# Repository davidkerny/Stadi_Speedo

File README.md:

Varianty pro Stadi_Speedo HW board:
__________________________________

MultiGauge od V1.8:

1. SPÍDO režim: (rychloměr) se ukazuje:
   pokud budík zaznamená jízdu.
   Pokud nějaké zaznamenal, ukáže i celkově ujeté km, trip km, max. km/h, otáčky motoru.
   Při rychlejší jízdě pro sichr skryje zbytečnosti.
3. TACHO režim (otáčkoměr)
   pokud zaznamenává otáčky motoru, ale ještě nikdy "nejel". Ukazuje Rpm + max. rpm.
4. Rev Mode (dočasný otáčkoměr)
   pokud už moped jel a tůruješ ho na místě; ukáže otáčky, max. rpm + trip km.

__
Ostatní / Historické okénko:
- Tacho V1 vychází ze Speedo V6
- MultiGauge V1 vychází ze Speedo V6 + Tacho V1
- AnaloGauge V1 vychází z MultiGauge V1.3
- ThermoGauge 0.1 vychází z MultiGauge 1.85 (vyžaduje Stadi_Speedo PCB V2)
- OBDGauge vychází z ThermoGauge 0.3

________________________
Varianty pro Waveshare ESP32-S3 2.1 TOUCH LCD board:

  - WS21 Gauge

_________________________

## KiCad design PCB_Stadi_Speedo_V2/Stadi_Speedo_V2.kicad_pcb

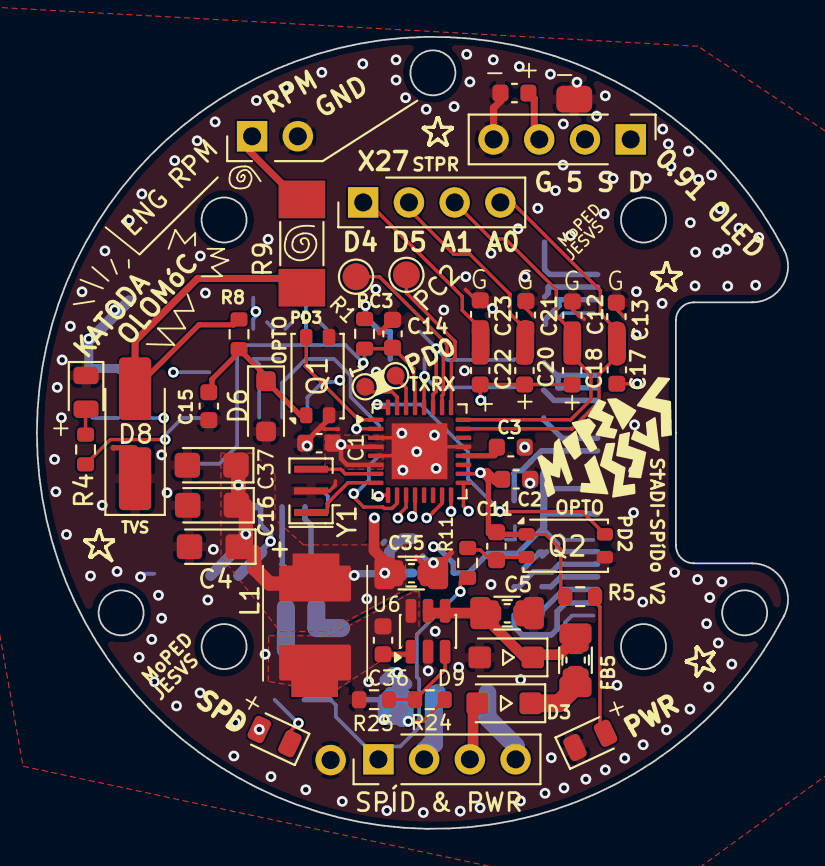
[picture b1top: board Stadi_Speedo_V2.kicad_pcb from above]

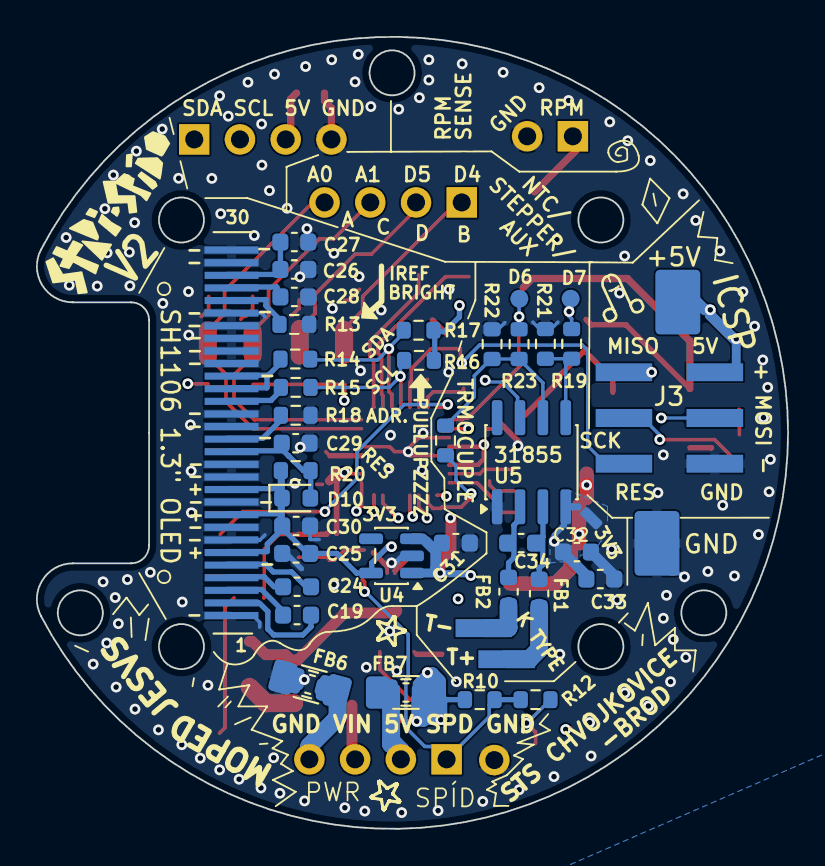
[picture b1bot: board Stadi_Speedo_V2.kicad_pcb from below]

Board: 4 copper layers, 41.7 x 44.0 mm, 86 parts (35 on the bottom side), 56 nets.

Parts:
C1, C2, C6, C19, C24, C25, C30, C31, C33: 1u; C_0603_1608Metric
C3, C11, C12, C13, C14, C17, C18, C20, C21, C22, C23, C29, C32, C34, C36: 100n; C_0603_1608Metric
C4, C16, C37: 4u7_16V; CP_EIA-3216-10_Kemet-I
C5: 4u7; C_0603-1206_universal_Pad1.18x1.45mm
C15: 10n; C_0603_1608Metric
C26, C27: 2.2u; C_0603_1608Metric
C28: 4.7u; C_0603_1608Metric
C35: 4u7_16V; C_0603-1206_universal_Pad1.18x1.45mm
D1, D7: Yellow; LED_0805_2012Metric
D2: Green; LED_0805_2012Metric
D3: D_Small; D_SOD-123FL
D6: 1N4148W; D_SOD-123F
D8: SMCJ85CA; D_SMA_Handsoldering
D9: PTVS8V5S1UTR-QX; D_SOD-123FL
D10: D_Small; D_0603_1608Metric
FB1, FB2: FerriteBead_Small; L_0603_1608Metric
FB5: FerriteBead_4A_180Ω; C_0603-1206_universal_Pad1.18x1.45mm
FB6, FB7: FerriteBead_4A_180Ω; C_0603-1206_universal_Pad1.33x1.80mm_HandSolder
J2: OLED I2C; PinHeader_1x04_P2.54mm_Vertical
J3: ICSP; PinHeader_2x03_P2.54mm_Vertical_SMD
J4: OLED SH1106; OLED-128O064D
J5: SPÍD & PWR; PinHeader_1x04_P2.54mm_Vertical
J6: AUX DDAA; PinHeader_1x04_P2.54mm_Vertical
J7: ENG RPM; PinHeader_1x02_P2.54mm_Vertical
L1: L_Ferrite; L_Bourns_SRP2313AA
Q1: 140817143200; Panasonic_APV-AQY_SSOP-4_4.45x2.65mm_P1.27mm
Q2: PC817; Panasonic_APV-AQY_SSOP-4_4.45x2.65mm_P1.27mm
R1, R4, R5, R12: 1k; R_0603_1608Metric
R8: 15k; R_0603_1608Metric
R9: 200R; R_MELF_MMB-0207
R10: 10k; R_0603_1608Metric
R11: 470R; R_0603_1608Metric
R13: 560K (390K); R_0603_1608Metric
R14, R15: 100R; R_0603_1608Metric
R16, R17, R20: 10k (4K7); R_0603_1608Metric
R18: 4K7; R_0603_1608Metric
R19, R23, R23#2: 10K; R_0603_1608Metric
R21, R22: 20K; R_0603_1608Metric
R24: 100k; R_0603_1608Metric
R25: 19.1k; R_0603_1608Metric
TP3, TP4: Label; TestPoint_Pad_D1.5mm
TP5, TP6: Label; TestPoint_Pad_D1.0mm
U1: Mikroprofesor; QFN-32-1EP_5x5mm_P0.5mm_EP3.1x3.1mm
U4: ME6211C33M5; SOT-23-5
U5: MAX31855KASA; SOIC-8_3.9x4.9mm_P1.27mm
U6: LMR51610YDBVR; SOT-23-6
Y1: 16MHz; Resonator_SMD_Murata_CSTxExxV-3Pin_3.0x1.1mm

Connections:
+3V3: C25.2, C30.2, C32.2, C33.2, D10.1 (K), J4.6, J4.9, J4.11, R20.2, U4.5 (V_{OUT}), U5.4 (V_{CC})
+5V: C1.1, C2.1, C4.1, C6.1, C11.1, C16.1, C17.1, C18.1, C20.1, C22.1, C31.2, C35.1, C37.1, D7.2 (A), FB7.1, J2.3, J3.2, L1.2, Q2.1, R1.2, R5.1, R10.2, R16.1, R17.2, R24.2, U1.4 (VCC), U1.6 (VCC), U1.18 (AVCC), U4.1 (V_{IN}), U4.3 (CE)
/A0: C13.1, C17.2, J6.4, U1.23 (PC0)
/A1: C12.1, C18.2, J6.3, U1.24 (PC1)
/ADDR: J4.15, R18.2
/D2_SPD: J5.1, R10.1, R11.2, R12.1
/D3_ENG_RPM: J7.1, R9.1
/D3_ENG_RPM_ISOL: Q1.4, U1.1 (PD3)
/D4: C22.2, C23.1, J6.1, U1.2 (PD4)
/D5: C20.2, C21.1, J6.2, U1.9 (PD5)
/D6/CS K: R23.2, R23#2.2, U1.10 (PD6)
/D7/SCK K: R19.2, U1.11 (PD7)
/D8/SO K: U1.12 (PB0), U5.7 (SO)
/D11/MOSI_: J3.4, U1.15 (PB3)
/D12/MISO_: J3.1, U1.16 (PB4)
/D13/SCK_: J3.3, R4.1, U1.17 (PB5)
/I2C_SCL: J2.2, R15.1, R16.2, U1.28 (PC5)
/I2C_SDA: J2.1, R14.1, R17.1, U1.27 (PC4)
/IREF BRIGHTNESS: J4.26, R13.2
/OLED RES: C29.2, D10.2 (A), J4.14, R20.1
/OLED SCLK: J4.18, R15.2
/OLED SDA: J4.19, J4.20, R14.2
/OLED VCC: C26.2, C27.2, J4.28
/PD0: TP5.1 (1_1), U1.30 (PD0)
/PD1: TP6.1 (1_1), U1.31 (PD1)
/RESET_: C14.1, J3.5, R1.1, U1.29 (~RESET/PC6)
/XTAL1: U1.7 (XTAL1/PB6), Y1.3
/XTAL2: U1.8 (XTAL2/PB7), Y1.1
/sw: C36.2, L1.1, U6.6 (SW)
GND: C1.2, C2.2, C3.2, C4.2, C5.2, C6.2, C12.2, C13.2, C14.2, C15.2, C16.2, C21.2, C23.2, C25.1, C26.1, C27.1, C28.1, C29.1, C30.1, C31.1, C32.1, C33.1, C35.2, C37.2, D1.1 (K), D2.1 (K), D6.2 (A), D8.1 (A1), D9.2 (A), FB6.1, J2.4, J3.6, J4.1, J4.7, J4.8, J4.10, J4.12, J4.13, J4.16, J4.17, J4.21, J4.22, J4.23, J4.24, J4.25, J4.29, J4.30, J7.2, Q1.2, Q1.3, Q2.3, R13.1, R18.1, R21.1, R22.1, R25.1, U1.3 (GND), U1.5 (GND), U1.21 (GND), U1.33 (GND), U4.2 (V_{SS}), U5.1 (GND), U6.2 (GND), Y1.2
unnamed: C11.2, Q2.2, R11.1
unnamed: D1.2 (A), R4.2
unnamed: D2.2 (A), R5.2
unnamed: C15.1, D6.1 (K), Q1.1, R8.1
unnamed: D7.1 (K), R12.2
unnamed: D8.2 (A2), R8.2, R9.2
unnamed: C5.1, D9.1 (K), FB5.2, U6.4 (EN), U6.5 (VIN)
unnamed: C19.2, J4.2
unnamed: C19.1, J4.3
unnamed: C24.2, J4.4
unnamed: C24.1, J4.5
unnamed: C28.2, J4.27
unnamed: FB7.2, J5.2
unnamed: FB6.2, J5.4
unnamed: C3.1, U1.20 (AREF)
unnamed: TP4.1 (1_1), U1.25 (PC2)
unnamed: TP3.1 (1_1), U1.26 (PC3)
unnamed: Q2.4, U1.32 (PD2)
unnamed: R19.1, R21.2, U5.5 (SCK)
unnamed: C34.2, FB1.2, U5.3 (T+)
unnamed: C34.1, FB2.2, U5.2 (T-)
unnamed: R22.2, R23.1, R23#2.1, U5.6 (~CS)
unnamed: C36.1, U6.1 (CB)
unnamed: R24.1, R25.2, U6.3 (FB)
VBUS: D3.2 (A), J5.3
VCC: D3.1 (K), FB5.1

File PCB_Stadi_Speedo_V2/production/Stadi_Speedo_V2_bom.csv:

Designator,Footprint,Quantity,Value,LCSC Part #
"_11, _10, _9, _8, _7, _6, _5, _4, _3, _2, ",,11,,
"C1, C19, C2, C24, C25, C30, C31, C33, C6",0603,9,1u,
"C11, C12, C13, C14, C17, C18, C20, C21, C22, C23, C29, C3, C32, C34, C36",0603,15,100n,
C15,0603,1,10n,
"C16, C37, C4",CP_EIA-3216-10_Kemet-I,3,4u7_16V,
"C26, C27",0603,2,2.2u,
C28,0603,1,4.7u,
C35,C_0603-1206_universal_Pad1.18x1.45mm,1,4u7_16V,
C5,C_0603-1206_universal_Pad1.18x1.45mm,1,4u7,
"D1, D7",0805,2,Yellow,C2296
D10,0603,1,D_Small,
D2,0805,1,Green,C2297
D3,D_SOD-123FL,1,D_Small,
D6,D_SOD-123F,1,1N4148W,
D8,D_SMA_Handsoldering,1,SMCJ85CA,
D9,D_SOD-123FL,1,PTVS8V5S1UTR-QX,
"FB1, FB2",0603,2,FerriteBead_Small,
FB5,C_0603-1206_universal_Pad1.18x1.45mm,1,FerriteBead_4A_180Ω,
"FB6, FB7",C_0603-1206_universal_Pad1.33x1.80mm_HandSolder,2,FerriteBead_4A_180Ω,
J2,PinHeader_1x04_P2.54mm_Vertical,1,OLED I2C,
J3,PinHeader_2x03_P2.54mm_Vertical_SMD,1,ICSP,
J4,OLED-128O064D,1,OLED SH1106,
J5,PinHeader_1x04_P2.54mm_Vertical,1,SPÍD & PWR,
J6,PinHeader_1x04_P2.54mm_Vertical,1,AUX DDAA,
J7,PinHeader_1x02_P2.54mm_Vertical,1,ENG RPM,
L1,L_Bourns_SRP2313AA,1,L_Ferrite,
Q1,Panasonic_APV-AQY_SSOP-4_4.45x2.65mm_P1.27mm,1,140817143200,
Q2,Panasonic_APV-AQY_SSOP-4_4.45x2.65mm_P1.27mm,1,PC817,
"R1, R12, R4, R5",0603,4,1k,
"R10, R19, R23_2, R23",0603,4,10k,
R11,0603,1,470R,
R13,0603,1,560K (390K),
"R14, R15",0603,2,100R,
"R16, R17, R20",0603,3,10k (4K7),
R18,0603,1,4K7,
"R21, R22",0603,2,20K,
R24,0603,1,100k,
R25,0603,1,19.1k,
R8,0603,1,15k,
R9,R_MELF_MMB-0207,1,200R,
U1,QFN-32-1EP_5x5mm_P0.5mm_EP3.1x3.1mm,1,Mikroprofesor,
U4,SOT-23-5,1,ME6211C33M5,
U5,SOIC-8_3.9x4.9mm_P1.27mm,1,MAX31855KASA,
U6,SOT-23-6,1,LMR51610YDBVR,
Y1,Resonator_SMD_Murata_CSTxExxV-3Pin_3.0x1.1mm,1,16MHz,

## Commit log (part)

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2026-06-30 Initial V2 Stadi Speedo
